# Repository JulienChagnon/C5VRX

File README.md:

<div align="center">

  <p><strong>ESP32-C5 Analog 5.8 GHz FPV Receiver</strong></p>
  <p>From live 5.8 GHz FPV video to real-time analog CVBS with one Seeed Studio XIAO ESP32-C5 and a passive resistor DAC.</p>

  <p>

  </p>

</div>

---

C5VRX-5 receives analog 5.8 GHz FPV video using the ESP32-C5's own radio
and outputs composite PAL/NTSC through a passive 6-bit resistor DAC.
It includes automatic gain control, quick baseline boot and manual calibration, an on-screen menu
and browser-based flashing and controls. The sync flywheel was removed on
2026-10-25 (it caused severe desyncs and poor range on the board).

This branch builds and boots **U80P64-R1 only**. U85Q, kp/LP switching and
`m/K/k/j/P/O/H` controls are retired; see [P64 integration and evidence](docs/P64.md).
The fixed R1 table has one positive NTSC observation; PAL, weak-signal/range
and the final cleanup still need hardware validation. This default is an
operator choice, not a hardware qualification claim.

The PR #254 **11p receive baseline** is now applied at startup and after
channel/bandwidth/AFC restores, before measured analog profiles and digital
mode 0. In this branch calibration is manual; a quick boot phase check and
passive health monitor may recommend CALIBRATE. Upgrades can invalidate older
tables without starting an automatic calibration. The noise-only bench result is not a measured
sensitivity/range gain; see [11p integration and limits](docs/FINDINGS.md#11p-receive-baseline-pr-254-integration-2026-10-24).

## Experimental firmware — flight safety warning

> [!WARNING]
> **C5VRX is an experimental FPV receiver. Bugs, signal loss, automatic
> receive-chain changes or incompatibility with your camera/goggles can cause
> sudden loss of video or sync, even after an apparently successful test.
> Loss of FPV video can lead to a crash, property damage or serious injury.**
> Do not rely on C5VRX as your only means of maintaining safe control of an aircraft.

- **Test every new firmware version and hardware/settings combination on the
  ground first.** Remove propellers for bench tests. Check startup and
  calibration, weak-signal behaviour, recovery after video loss, and your actual
  camera/goggles. Complete calibration before takeoff.
- **Keep disruptive controls on the ground:** calibration, scanning, channel
  changes, menu entry/exit, DAC tests and diagnostics can interrupt or replace
  the live picture. Do not flash firmware or run bench tests during flight.
- **Automatic changes are experimental too.** Live filter/profile switching is
  currently documented as enabled by default and awaiting board validation.
  It restarts part of the receive chain and may interrupt video. Console
  `A` disables live profile switching (report-only mode); confirm the state
  with `T` on your build. Live OUTPUT, format and profile changes restart the pipeline. These settings do not establish flight safety.
- If you proceed to flight testing, use a controlled area clear of people,
  traffic and property, keep the aircraft close, and have a safe way to recover
  control if video disappears. Follow applicable local rules, including visual
  line-of-sight and observer requirements.
- **A versioned release, a “Latest” label or passing CI is not flight
  qualification.** Unmerged PR builds are development builds. Check the exact
  build's documented hardware and flight-test evidence; a test of an earlier
  build does not validate later changes.
- Report unexpected video loss with the exact firmware version/commit, hardware,
  settings, reproduction steps and any available logs/DVR footage. Preserve
  evidence after an incident, and investigate on the ground before flying again.

The firmware is provided under [GPL-3.0-only](LICENSE), including its warranty
and liability provisions in sections 15–17, to the extent permitted by
applicable law. This warning does not replace those terms or limit rights
that cannot legally be excluded.

## Video

[Watch the C5VRX-5 vs C5VRX-4 flight range test by Louis Hitchcock](https://www.youtube.com/watch?v=Gp3xmLrn_34).

## Hardware

XIAO ESP32-C5. DAC on D4..D9 (GPIO 23, 24, 11, 12, 8, 9; LSB first) with
8.2k / 3.9k / 2k / 1k / 470R / 240R and a 200R load, as in C5VRX-3/4
([schematic](docs/hardware/c5vrx-dac-schematic.png)). The
receiver uses the ESP32-C5's own Wi-Fi radio; no extra RF parts.

Other ESP32-C5 boards (Espressif DevKitC-1, Waveshare ESP32-C5-Pico, NiceMCU
ESP32-C5 Mini) have their own pin maps and images, and any other ESP32-C5
board can be flashed with its own pins from the web flasher's pin editor.
None of them is tested on hardware yet. The flasher draws each board with
the resistor for every pin. See [Boards](docs/BOARDS.md).

This development build moves the internal I-LSB loopback from D10/GPIO10
to the user-LED GPIO27, and the Q-sign loopback from D3/GPIO7 to GPIO2.
This reserves **D10 and D3 for future seventh/eighth DAC branches**. The LED
may glow during reception. No external IQ wiring is needed; the active DAC
remains 6-bit and the extra resistor footprints must stay **unpopulated (DNP)**.

| Reserved extra branch | XIAO pin / GPIO | Nominal resistor to CVBS | Future significance |
| --- | --- | --- | --- |
| Seventh branch | D10 / GPIO10 | 15 kOhm | 7-bit: bit 0; 8-bit: bit 1 |
| Eighth branch | D3 / GPIO7 | 33 kOhm | 8-bit: bit 0 (LSB) |

“Seventh/eighth” counts physical branches; these are added **low** bits,
not new MSBs. Existing D4..D9 branches become bits 1..6 for 7-bit or 2..7
for 8-bit. These are reserved footprints, not enabled output lanes or a
validated 7/8-bit resistor network. Wider output needs firmware and loaded
CVBS level/linearity checks. D3/GPIO7 is a boot strap: check reset loading
before populating its branch. GPIO2 is now IQ-owned and cannot also carry
the optional sample clock from PR #257. Both new IQ routes still require
board validation. The operator reported unsatisfactory behavior with the
LED-pin IQ route; this PR isolates it for comparison, not hardware acceptance.
See [the pin-routing findings](docs/FINDINGS.md#gpio27-iq-loopback-experiment-2026-10-25).

### Wiring the resistor DAC

Six resistors, one per XIAO pin, all joined on one node: that node is the
video output (CVBS). A seventh resistor from that node to GND is the load.

| XIAO pin | GPIO | DAC bit | resistor to the output node |
| --- | ---: | --- | ---: |
| D4 | 23 | bit 0 (LSB) | 8.2 kΩ |
| D5 | 24 | bit 1 | 3.9 kΩ |
| D6 | 11 | bit 2 | 2.0 kΩ |
| D7 | 12 | bit 3 | 1.0 kΩ |
| D8 | 8 | bit 4 | 470 Ω |
| D9 | 9 | bit 5 (MSB) | 240 Ω |
| GND | - | load | 200 Ω (output node to GND) |

```
D4 --[8.2k]--+
D5 --[3.9k]--+
D6 --[2.0k]--+
D7 --[1.0k]--+-----------> CVBS out (goggle / monitor AV-in, video)
D8 --[470R]--+     |
D9 --[240R]--+   [200R]   (optional: 470 pF from the node to GND,
                   |        improvement unproven)
GND ---------------+------> GND (goggle / monitor AV-in ground)
```

- The pin order matters: the largest resistor (8.2k) goes on D4 and the
  smallest (240R) on D9. A swapped pair gives a scrambled, banded picture.
- Connect the output node to the video input (centre/tip) of the goggles,
  a DVR or an analog monitor, and the XIAO GND to its ground. A common
  ground is required.
- All values are standard E24; 1 % metal-film resistors are fine. Keep
  the wires from the pins to the node short.
- Too dark or too dim on some goggles: try OUTPUT in the menu (0.5-5.0x,
  saved). Higher levels can clip; check the loaded output on your display.
- The XIAO is powered over USB-C or its 5 V pin as usual; the DAC needs no
  separate supply.
- **Check the build with the DAC self-test** before chasing picture
  problems: a test pattern for the goggles and a multimeter check that names
  a swapped, open or wrong resistor. See
  [Building and testing the resistor DAC](docs/hardware/dac-build-and-test.md).

### DIY Carrier PCB — REV C: Fat Shark Module + 3.5 mm AV Jack

**[C5VRX_JACK_DIY_V3 / REV C](hardware/C5VRX_JACK_DIY_V3)** is the latest proposed DIY carrier revision for the Seeed Studio XIAO ESP32-C5. It keeps the REV B layout (Fat Shark module-bay outline, 3.5 mm PJ-320D AV jack, reserved seventh/eighth DAC branches) and replaces the SJ1 bay-power solder bridge with a through-hole 1N5819 Schottky diode, so USB and the goggle bay can be connected at the same time.

<div align="center">

</div>

| Feature | REV C details |
| --- | --- |
| **Form factor** | 42.51 × 28.80 mm; XIAO, AV jack and bay header keep their REV A positions |
| **AV output** | VIDEO on Fat Shark J1 pin 6 and PJ-320D tip + ring 1; ground on the jack sleeve |
| **Through-hole DAC** | DIN0207 axial ¼ W resistors; existing six branches and 200 Ω shunt retained |
| **Reserved DAC expansion** | R8: 15 kΩ from D10/GPIO10 via SJ2; R9: 33 kΩ from D3/GPIO7 via SJ3 |
| **Bay power** | D1: 1N5819 Schottky (DO-41, through-hole) from bay 5 V to XIAO 5 V; no jumper to open before USB programming |
| **Rear solder jumpers** | SJ2 / BIT 7 and SJ3 / BIT 8: extra DAC branches |
| **Artwork** | C5VRX logos on both sides; REV C and 6–8 BIT DAC markings on the back |

**Current firmware remains six-bit:** leave R8/R9 unpopulated and SJ2/SJ3 open. The jumpers connect hardware only; seven/eight-bit output still needs matching firmware and electrical validation. [Assembly and jumper settings](hardware/C5VRX_JACK_DIY_V3#dac-branches-and-rear-jumpers).

**Downloads:** [Gerbers + drills](hardware/C5VRX_JACK_DIY_V3/exports/C5VRX_JACK_DIY_V3-gerbers.zip) · [KiCad project](hardware/C5VRX_JACK_DIY_V3) · [BOM](hardware/C5VRX_JACK_DIY_V3/BOM.csv) · [Schematic PDF](hardware/C5VRX_JACK_DIY_V3/exports/C5VRX_JACK_DIY_V3-schematic.pdf) · [STEP](hardware/C5VRX_JACK_DIY_V3/exports/C5VRX_JACK_DIY_V3.step) · [Renders](hardware/C5VRX_JACK_DIY_V3/exports/renders/).

KiCad ERC/DRC and schematic/PCB parity checks are clean; REV C has not been built or measured. [REV B](hardware/C5VRX_JACK_DIY_V2) and the original [REV A carrier](hardware/C5VRX_JACK_DIY) remain available with their fabrication files.

## Flashing

- **Browser:** open the [web flasher](https://twotoz.github.io/C5VRX/) in
  desktop Chrome or Edge, choose **C5VRX-5**, a build and your **Board**,
  connect, then flash. **Flash and PSRAM** on Auto picks the image from the
  connected chip (PSRAM if the chip has it, a 4 MB layout on 4 MB flash) and
  refuses an image that does not fit. It shows where each resistor goes on
  the selected board, and **Custom pins** writes other GPIOs into the
  image ([Boards](docs/BOARDS.md)).
  Use **Full firmware** when switching from another generation or image.
  Unmerged PR builds are marked as development builds.
- **From source:** use ESP-IDF **6.0.2**, run `idf.py build` in the
  repository root, then `python tools/flash.py PORT` (for example `COM6`
  or `/dev/ttyACM0`). Filter and DC correction require its exact libphy;
  other PHY versions disable them and produce a build warning.
  Do not use `idf.py flash` on a running receiver: its USB line reset hangs
  the board (pySerial "Write timeout") until USB and battery are removed.
  `tools/flash.py` asks the firmware for download mode with the `` ` `` key,
  flashes without a line reset and restarts through the watchdog. If the
  board is already in the ROM loader (BOOT held while plugging in), add
  `--no-key`. `--app-only` flashes only the app image, which is faster
  when the bootloader and partition table have not changed, and
  `--monitor` then shows the console without resetting the chip (use it
  instead of `idf.py flash monitor`; `--monitor-only` opens it without
  flashing). `--log FILE` keeps a timestamped copy of the console,
  `--iq DIR` saves each IQ snapshot (key `I`, or every N seconds with
  `--iq-every N`) as `.bin` + `.json`, and `--check` waits for the boot,
  runs `T` and `D` and exits 1 if the board crashed, runs a different
  image than the one flashed, or reports a chain fault (low heap only
  warns). Before flashing it warns when the build's `sdkconfig` differs
  from `sdkconfig.defaults`: ESP-IDF keeps an existing `sdkconfig`, so
  delete it and rebuild after the defaults change.
- **Local File** flashes your own `.bin`; **Legacy builds** contains archived
  C5VRX-3 firmware.

## XIAO PSRAM image

The standard image also supports boards without PSRAM. For a XIAO
ESP32-C5HR8 with 8 MB PSRAM, every release also has a PSRAM image, which the
web flasher picks on Auto. To build it with ESP-IDF 6.0.2:

```sh
idf.py -B build-psram -DSDKCONFIG=sdkconfig.psram "-DSDKCONFIG_DEFAULTS=sdkconfig.defaults;sdkconfig.psram.defaults" build
python tools/flash.py PORT --build build-psram --check
```

Use a fresh `sdkconfig.psram` when changing these defaults. Flash the full image
when switching configurations, including the matching bootloader. This image
requires PSRAM and will panic on a board without it. The contributor measured
boot `heap_min` rising from about 2.1 KB to 21.9 KB on the XIAO; PAL and long-run
checks remain pending. The live DMA/video buffers stay in internal RAM.
See [PSRAM measurements and limits](docs/FINDINGS.md#psram-8-mb-on-the-xiao-now-mapped-board-2026-10-26).

## First boot

1. Power the receiver: it loads saved values or a fixed baseline. A bounded
   sampling-phase check runs under the boot logo; no automatic RF/DC sweep.
2. If repeated measurements show a poor baseline, the menu shows a calibration
   recommendation. Use **CALIBRATE** on the ground, preferably with the VTX off.
   Menu calibration measures the current normal filter; **Full RF optimization**
   in the web controls is a separate, longer bench operation.
3. Select the VTX channel or use SCAN. Without a saved channel it starts on A1.
4. For multi-board testing, use **CALIBRATE → Download calibration report** in
   the connected web controls. This reads data without changing settings.
   See [measurement protocol and timing evidence](docs/FASTER_CALIBRATION.md).

## Controls (BOOT button)

| Action | Live video | Menu |
| --- | --- | --- |
| Short press | Next channel | Next item |
| Hold 0.6 s | Open menu | Select item |

The menu is one black-and-white settings list with every row in view:
**BAND**, **CHANNEL**, **SCAN**, **VIDEO** (AUTO/NTSC/PAL),
**CALIBRATE**, **OUTPUT** (0.5-5.0x), **GAIN** (AUTO/LEVEL/RSSI/MAX/fixed),
**DAC TEST** and **EXIT**, each with its current value. A card beside the
list keeps the frequency, signal and level in view and names what a hold
does. Every boot shows the C5VRX logo while Direct Gain finds its first
gain: the bar fills over 3 s (up to 4 s while the gain has not
held yet), so live video starts on a settled gain.
It closes after 30 seconds of
inactivity, or five minutes in DAC TEST. Menu transitions can interrupt video.
GAIN starts in AUTO (KEEL-1) on every boot. LEVEL and RSSI are research AGC
models for a side-by-side comparison on your own setup (docs/FINDINGS.md,
"AGC research"); they are simulated, not yet proven on the board.

## Serial console (USB, 115200)

Use the web flasher's **Terminal** tab for receiver controls and logs,
or a serial terminal at 115200 baud. Keys are case-sensitive and sent
without Enter; `h` lists the commands supported by your firmware.

| Key | Action |
| --- | --- |
| `T` / `h` | Status / help |
| `b` / `c` / `s` | Next band / next channel / scan |
| `o` / `n` / `x` / `e` | Open menu / next item / select / exit |
| `v` / `g` / `G` | Video standard / output level / gain |
| `F` / `B` / `C` | Calibrate current filter / full RF optimization / read-only calibration report |
| `Z` | DAC self-test (ground only) |
| `D` / `R` | Health report / per-second field diagnostics |
| `I` / `M` / `L` | IQ snapshot / gain map / bench IQ lane test |
| `A` | Live analog filter/profile switching on/off (saved) |
| `S` + suite | Bench PHY sensitivity lab, VTX on ([docs](docs/PHY_SENSITIVITY_LAB.md); ground only) |
| `` ` `` | USB download mode |

P64 always uses the same fixed program and LUT. Profiles select only the
analog filter (DEFAULT, NARROW or WIDE); old `kp_auto` and `lp_cn` settings
are ignored. `A` toggles experimental live profile switching (default on).
Live OUTPUT and profile changes share a five-second
cooldown and verified halted restart/rollback. Higher OUTPUT levels can clip.
GAIN always starts AUTO at boot; the OUTPUT preference is saved.
Check `T` after changing settings. Retired models remain research only.

The browser terminal and flasher use the port one at a time. **Download log**
saves the displayed output; only the latest 120,000 characters are retained.

## Documentation and development

- [DAC build and self-test guide](docs/hardware/dac-build-and-test.md)
- [REV C Fat Shark carrier PCB, power diode, jumpers and fabrication files](hardware/C5VRX_JACK_DIY_V3)
- [REV B carrier](hardware/C5VRX_JACK_DIY_V2)
- [REV A carrier archive](hardware/C5VRX_JACK_DIY)
- [Receiver findings and hardware evidence](docs/FINDINGS.md)
- [Field-test protocol](docs/FIELD_TEST.md)
- [Current receiver changes and validation](docs/PR212.md)
- [U85Q research](docs/pr190-key-findings.md) and [research index](research/README.md)
- [Contributing](CONTRIBUTING.md)

`main/` contains C5VRX-5 firmware, `web/` the GitHub Pages flasher,
`test/` host tests, `docs/` guides and findings, `research/` experiments,
and `tools/` console and CI helpers. `legacy/` preserves C5VRX-1 through
C5VRX-4 as reference; they are not built.

CI runs host/research checks and builds firmware with ESP-IDF 6.0.2.
Firmware changes publish versioned `c5vrx5-v5.0.N` releases or unmerged
`c5vrx5-pr-N` builds. Website-only changes do not create firmware releases.
Pages deploys the website from `main` with a same-origin firmware mirror.
Firmware PRs need passing checks and board tests on the matching artifact;
host tests alone do not establish picture compatibility or RF range.

## Community

Share build photos, questions and feedback on the
[C5VRX Discord](https://discord.gg/3YNgJRHmzD).

## Credits and license

C5VRX-5 is part of [C5VRX](https://github.com/Twotoz/C5VRX) by Twotoz and
the C5VRX contributors; the official website
([twotoz.github.io/C5VRX](https://twotoz.github.io/C5VRX/)) has the project
and its Discord invite. It builds on C5VRX-2..4 (the continuous MODEM_DIAG
to BitScrambler video path, Direct Gain V3-V5, the PAIR schedule and the
U85Q study of PR #190), on zerowidth/C5VRX PR #3 (interference-burst gate,
sampling-phase probe, off-grid channel tuning), on Louis Hitchcock's staged
overload recovery (C5VRX #182/#184), and on ESPARGOS esp-sdr (GPL-3.0) for
the C5 RX filter control. Espressif supplied the GDMA EOF fix
(espressif/esp-idf#19091).

Like the rest of this repository, C5VRX-5 is licensed under
**GPL-3.0-only** (see [LICENSE](LICENSE)). The GPL allows
commercial use, including selling receivers with this firmware, provided
the source (with your changes) is passed on under the same license.

The C5VRX name and logos have separate terms; see [assets/BRANDING.md](assets/BRANDING.md).

## Build components

| Product | Photo | Link / Source |
| --- | --- | --- |
| Seeed Studio XIAO ESP32-C5 |  | [View on Amazon](https://link.amazon/B0gopCVDt) |
| C5VRX_JACK_DIY_V3 / REV C carrier |  | [Gerbers & KiCad files](hardware/C5VRX_JACK_DIY_V3) · [REV B](hardware/C5VRX_JACK_DIY_V2) · [REV A](hardware/C5VRX_JACK_DIY) |
| Perfboard (alternative) |  | [View on Amazon](https://link.amazon/B0i2qqMeq) |
| Resistor kit |  | [View on Amazon](https://link.amazon/B06XSBkln) |

Affiliate links. As an Amazon Associate, I earn from qualifying purchases.
All affiliate earnings go back into C5VRX development.

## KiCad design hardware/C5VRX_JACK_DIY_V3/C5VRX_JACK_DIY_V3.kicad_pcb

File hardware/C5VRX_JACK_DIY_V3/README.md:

# C5VRX_JACK_DIY_V3 — REV C

A two-layer DIY carrier for the Seeed Studio XIAO ESP32-C5, with a Fat Shark module-bay header and PJ-320D 3.5 mm AV jack. REV C keeps the REV B outline (42.51 × 28.80 mm), part positions and DAC branches, and replaces the SJ1 bay-power solder bridge with a through-hole Schottky diode.

## Downloads

| File | Link |
| --- | --- |
| Gerber X2 + Excellon drills | [Fabrication ZIP](exports/C5VRX_JACK_DIY_V3-gerbers.zip) |
| KiCad 10 source | [Project](C5VRX_JACK_DIY_V3.kicad_pro) · [PCB](C5VRX_JACK_DIY_V3.kicad_pcb) · [Schematic](C5VRX_JACK_DIY_V3.kicad_sch) |
| Parts and assembly flags | [BOM](BOM.csv) |
| Schematic and fit check | [Schematic PDF](exports/C5VRX_JACK_DIY_V3-schematic.pdf) · [1:1 PDF](exports/C5VRX_JACK_DIY_V3-fit-check-1to1.pdf) |
| Mechanical models | [STEP](exports/C5VRX_JACK_DIY_V3.step) · [GLB](exports/C5VRX_JACK_DIY_V3.glb) |
| High-resolution images | [Front](exports/renders/01-front-perspective.png) · [Back](exports/renders/02-back-perspective.png) · [Low angle](exports/renders/05-front-low-angle.png) · [All five as ZIP](exports/C5VRX_JACK_DIY_V3-renders.zip) |

## Changes from REV B

- **D1 replaces SJ1.** A 1N5819 Schottky diode (1 A / 40 V, DO-41; a 1N5817 also fits) connects bay 5 V (anode) to XIAO 5 V (cathode). Bay power no longer needs a solder bridge, and there is no jumper to open before USB programming: the diode stops USB 5 V from feeding the goggle bay.
- D1 lies flat on the front, between the AV jack and the resistor bank, with its holes on the same row as R7 (y = 123 mm). Fit it with the **band (cathode) toward the K mark**, on the jack side.
- D1 uses a project footprint (`C5VRX:D_DO-41_P7.62mm_Horizontal_Compact`): 7.62 mm lead pitch, 1.7 mm pads and 1.0 mm drills, so its courtyard fits between the jack and the resistor bank.
- To make room, bay 5 V now runs on the front along the bottom edge, the BIT 8 trace (SJ3 to R9) runs on the back underneath D1, between its pads, and one redundant GND via next to R7 was removed (R7's ground pad connects to both ground pours).
- The rear jumpers are symmetric: SJ2 (BIT 7) sits on the R5 row and SJ3 (BIT 8) on the R3 row, at the same position across, mirrored around the middle of the resistor bank, with their labels on the outside. The BIT 7 traces were rerouted for the new SJ2 position.
- The rear marking reads REV C, and the SJ1 label is gone.

The XIAO's 5 V rail is about 0.3 V lower on bay power (diode drop); the XIAO regulates its own 3.3 V from it. With USB and the bay connected at the same time, the higher of the two supplies feeds the XIAO.

## DAC branches and rear jumpers

| Jumper | Function | Default |
| --- | --- | --- |
| SJ2 / BIT 7 | Connect D10 / GPIO10 through R8 (15 kΩ) to VIDEO | Open |
| SJ3 / BIT 8 | Connect D3 / GPIO7 through R9 (33 kΩ) to VIDEO | Open |

R8 is **15 kΩ** and R9 is **33 kΩ**; R1–R7 and the 200 Ω load are unchanged. R8 and R9 are **DNP** with the current six-bit firmware. The jumpers only connect hardware branches; they do not select a firmware mode. These are new **low bits**: in a future seven-bit implementation D10 is bit 0; in an eight-bit implementation D10 is bit 1, D3 is bit 0, and the existing D4–D9 outputs are bits 2–7.

| Output configuration | SJ2 | SJ3 | Additional resistors |
| --- | --- | --- | --- |
| Current six-bit | Open | Open | R8/R9 DNP |
| Future seven-bit | Closed | Open | Fit R8 |
| Future eight-bit | Closed | Closed | Fit R8 and R9 |

Wider output requires matching firmware and loaded CVBS level/linearity measurements; it is not enabled or hardware-qualified by this PCB. D3/GPIO7 is a boot-strapping pin: validate repeated cold boots and reset loading before fitting/enabling R9. Keep the extra resistors unpopulated and jumpers open with current firmware.

R1–R7 retain the existing 8.2 kΩ / 3.9 kΩ / 2 kΩ / 1 kΩ / 470 Ω / 240 Ω branches and 200 Ω shunt. All resistors use DIN0207 axial through-hole footprints, 10.16 mm lead pitch; 1% is recommended. C1 is optional 470 pF / DNP. No additional 75 Ω shunt is fitted. J2 tip and ring 1 carry VIDEO, sleeve is GND, and ring 2 is unconnected.

## Files and checks

- Open `C5VRX_JACK_DIY_V3.kicad_pro` in **KiCad 10**. Project symbol/footprint libraries (including the D1 footprint) and the PJ-320D STEP model are included.
- [Fabrication ZIP](exports/C5VRX_JACK_DIY_V3-gerbers.zip): Gerber X2 plus plated/non-plated Excellon drills, ready to upload to a PCB fab.
- [BOM](BOM.csv): PCB values, DNP flags and open rear solder bridges (PCB features, not purchased components).
- [Schematic PDF](exports/C5VRX_JACK_DIY_V3-schematic.pdf), [1:1 fit-check PDF](exports/C5VRX_JACK_DIY_V3-fit-check-1to1.pdf), STEP and GLB models are in `exports/`.
- [3200 × 2200 renders](exports/renders/) and [render ZIP](exports/C5VRX_JACK_DIY_V3-renders.zip). The XIAO mounting outline is visible because no module 3D model is supplied; DNP parts are omitted.
- [DRC report](validation/drc.json) and [ERC report](validation/erc.json): zero errors, zero unrouted connections and zero schematic/PCB parity issues. Generated with KiCad 10.0.7.

Digital checks are not physical qualification. REV C has not yet been built or measured. [REV B](../C5VRX_JACK_DIY_V2/) and [REV A](../C5VRX_JACK_DIY/) remain available.

## Source and attribution

This carrier adapts the existing `hardware/C5VRX_JACK_DIY` and `hardware/C5VRX_JACK_DIY_V2` (REV B) boards and DAC design from **C5VRX by Twotoz and the C5VRX contributors**. REV C replaces the SJ1 power jumper with the D1 Schottky diode and reroutes the affected 5 V and BIT 8 traces; the D1 footprint is derived from KiCad's `Diode_THT:D_DO-41_SOD81_P7.62mm_Horizontal` with smaller pads.

Canonical source: [Twotoz/C5VRX](https://github.com/Twotoz/C5VRX). Visit the [official C5VRX website](https://twotoz.github.io/C5VRX/) for the project and its Discord invite. Applicable source terms are in [LICENSE](../../LICENSE); separate name/logo terms remain in [BRANDING.md](../../assets/BRANDING.md). This proposed hardware revision is not a claim of an already released or physically validated product.

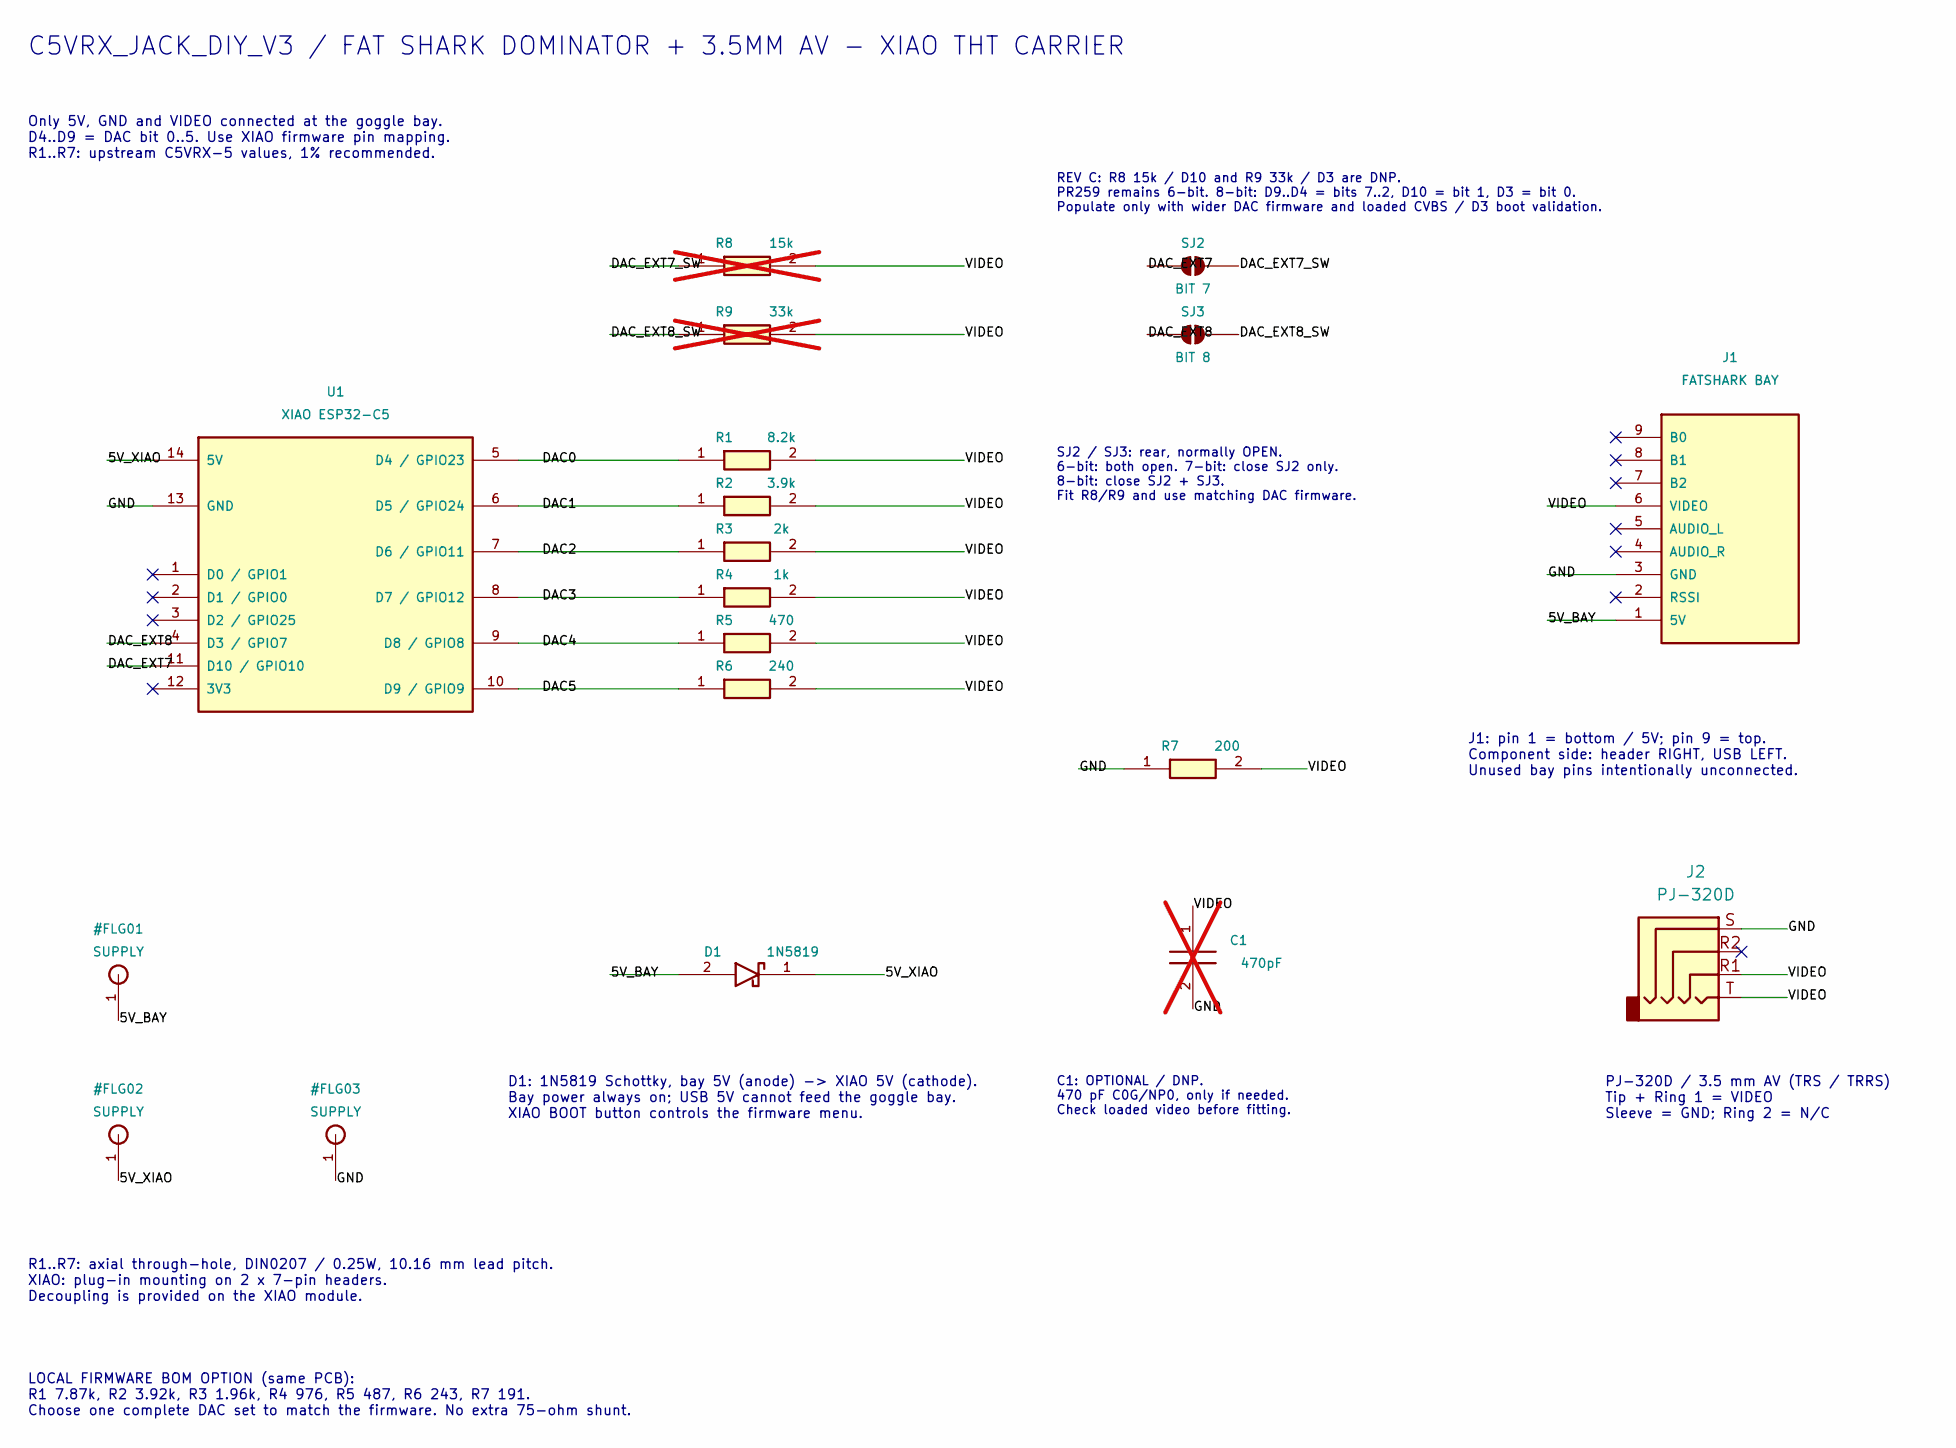
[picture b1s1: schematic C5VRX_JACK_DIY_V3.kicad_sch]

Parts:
C1: 470pF; C_Disc_D3.0mm_W1.6mm_P2.50mm; not fitted
D1: 1N5819; D_DO-41_P7.62mm_Horizontal_Compact
J1: FATSHARK BAY; FatShark_Header_1x09
J2: PJ-320D; Jack_3.5mm_PJ320D_Horizontal
R1: 8.2k; R_Axial_DIN0207_L6.3mm_D2.5mm_P10.16mm_Horizontal
R2: 3.9k; R_Axial_DIN0207_L6.3mm_D2.5mm_P10.16mm_Horizontal
R3: 2k; R_Axial_DIN0207_L6.3mm_D2.5mm_P10.16mm_Horizontal
R4: 1k; R_Axial_DIN0207_L6.3mm_D2.5mm_P10.16mm_Horizontal
R5: 470; R_Axial_DIN0207_L6.3mm_D2.5mm_P10.16mm_Horizontal
R6: 240; R_Axial_DIN0207_L6.3mm_D2.5mm_P10.16mm_Horizontal
R7: 200; R_Axial_DIN0207_L6.3mm_D2.5mm_P10.16mm_Horizontal
R8: 15k; R_Axial_DIN0207_L6.3mm_D2.5mm_P10.16mm_Horizontal; not fitted
R9: 33k; R_Axial_DIN0207_L6.3mm_D2.5mm_P10.16mm_Horizontal; not fitted
SJ2: BIT 7; SolderJumper-2_P1.3mm_Open_Pad1.0x1.5mm
SJ3: BIT 8; SolderJumper-2_P1.3mm_Open_Pad1.0x1.5mm
U1: XIAO ESP32-C5; XIAO-ESP32-C5-DIP

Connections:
/5V_BAY: D1.2 (A), J1.1 (5V)
/5V_XIAO: D1.1 (K), U1.14 (5V)
/DAC0: R1.1, U1.5 (D4 / GPIO23)
/DAC1: R2.1, U1.6 (D5 / GPIO24)
/DAC2: R3.1, U1.7 (D6 / GPIO11)
/DAC3: R4.1, U1.8 (D7 / GPIO12)
/DAC4: R5.1, U1.9 (D8 / GPIO8)
/DAC5: R6.1, U1.10 (D9 / GPIO9)
/DAC_EXT7: SJ2.1 (A), U1.11 (D10 / GPIO10)
/DAC_EXT7_SW: R8.1, SJ2.2 (B)
/DAC_EXT8: SJ3.1 (A), U1.4 (D3 / GPIO7)
/DAC_EXT8_SW: R9.1, SJ3.2 (B)
/GND: C1.2, J1.3 (GND), J2.S, R7.1, U1.13 (GND)
/VIDEO: C1.1, J1.6 (VIDEO), J2.R1, J2.T, R1.2, R2.2, R3.2, R4.2, R5.2, R6.2, R7.2, R8.2, R9.2

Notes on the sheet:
C5VRX_JACK_DIY_V3 / FAT SHARK DOMINATOR + 3.5MM AV - XIAO THT CARRIER
Only 5V, GND and VIDEO connected at the goggle bay. D4..D9 = DAC bit 0..5. Use XIAO firmware pin mapping. R1..R7: upstream C5VRX-5 values, 1% recommended.
J1: pin 1 = bottom / 5V; pin 9 = top. Component side: header RIGHT, USB LEFT. Unused bay pins intentionally unconnected.
D1: 1N5819 Schottky, bay 5V (anode) -> XIAO 5V (cathode). Bay power always on; USB 5V cannot feed the goggle bay. XIAO BOOT button controls the firmware menu.
R1..R7: axial through-hole, DIN0207 / 0.25W, 10.16 mm lead pitch. XIAO: plug-in mounting on 2 x 7-pin headers. Decoupling is provided on the XIAO module.
LOCAL FIRMWARE BOM OPTION (same PCB): R1 7.87k, R2 3.92k, R3 1.96k, R4 976, R5 487, R6 243, R7 191. Choose one complete DAC set to match the firmware. No extra 75-ohm shunt.
C1: OPTIONAL / DNP. 470 pF C0G/NP0, only if needed. Check loaded video before fitting.
PJ-320D / 3.5 mm AV (TRS / TRRS) Tip + Ring 1 = VIDEO Sleeve = GND; Ring 2 = N/C
REV C: R8 15k / D10 and R9 33k / D3 are DNP. PR259 remains 6-bit. 8-bit: D9..D4 = bits 7..2, D10 = bit 1, D3 = bit 0. Populate only with wider DAC firmware and loaded CVBS / D3 boot validation.
SJ2 / SJ3: rear, normally OPEN. 6-bit: both open. 7-bit: close SJ2 only. 8-bit: close SJ2 + SJ3. Fit R8/R9 and use matching DAC firmware.

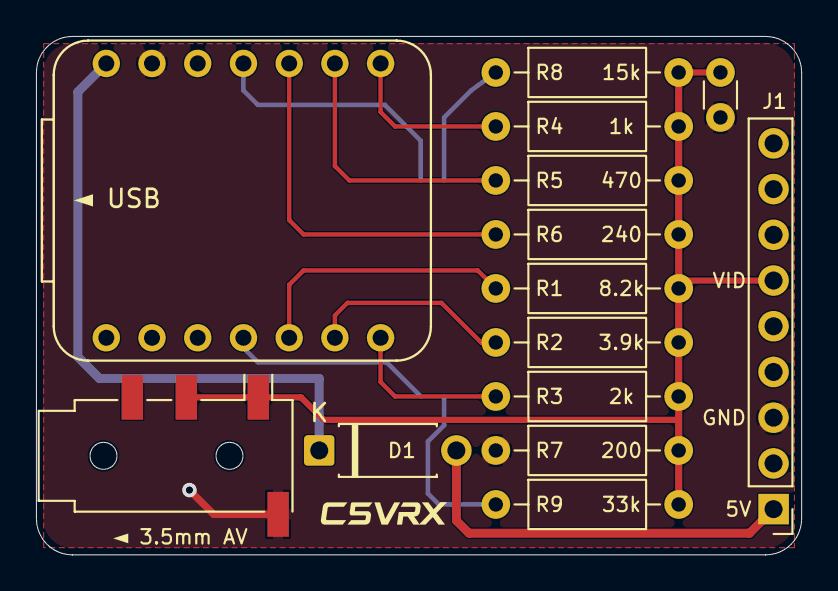
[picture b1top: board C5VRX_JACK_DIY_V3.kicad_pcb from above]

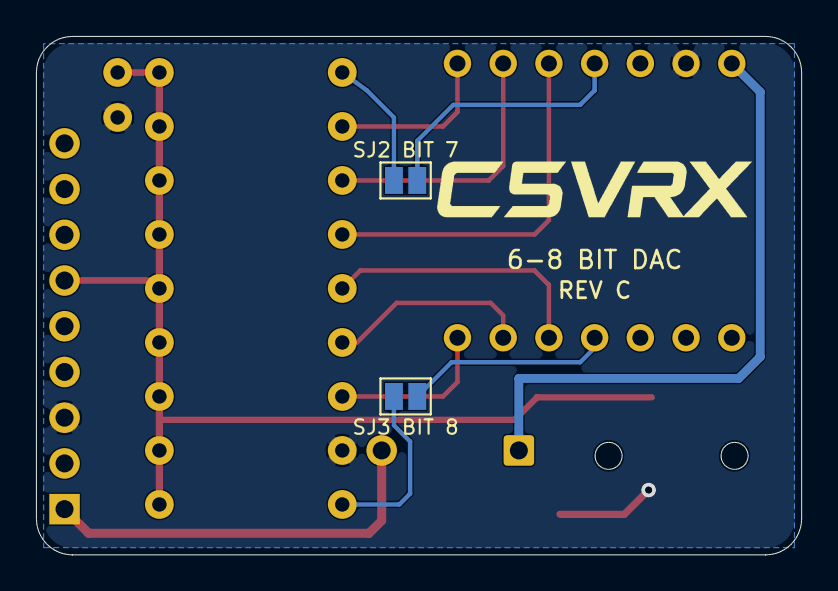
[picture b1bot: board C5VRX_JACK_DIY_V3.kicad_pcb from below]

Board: 2 copper layers, 42.5 x 28.8 mm, 18 parts (2 on the bottom side), 14 nets.

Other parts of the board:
LOGO1: C5VRX logo; C5VRX_Logo_Back
LOGO2: C5VRX Front Logo; C5VRX_Logo_Front_Small
